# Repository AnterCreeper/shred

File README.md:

# SHRED: (S)ystem for (H)igh-performance (R)eal-time (E)lectric guitar (D)igital effects

If you have any questions, feel free to open Issues & PRs.

**WARNING! This project has not been fully tested in long-term production environments and is provided without warranty of any kind. Use at your own risk!**

## License

This project is licensed under the LGPL-2.1-or-later license.

**DO NOT** download or clone this project until you have read and agreed to the LICENSE.

## TODO

1. plug subboard designs
2. FPGA RTL integration
3. controller firmware

## Overview

This project implements an audio system for electric guitars and consists of essential components, including the hardware (core and plug) with Gerber files and schematics, digital logic designs, mechanical designs for the pickguard, and firmware for a low-power microcontroller that provides HMI and system controls.

The TFT screen is not included, which is from Waveshare ([Click here](https://www.waveshare.net/wiki/1.9inch_LCD_Module)) and would be easy to obtain.

## Functions

- Audio Record & Playback (SD Card)
- Audio Mixer
- USB Audio Input and Output
- Wireless BLE Real-time Audio Monitor
- Audio Effects (chorus, distortion, EQ...)

## Directory

### Core

This directory contains PCB designs (KiCad) for the main board, which implements most functions. It includes battery management (TI `BQ25601` charger with `TPD2S300` for Type-C PD high-voltage fast charging, and TI `BQ27720` energy gauge), system microcontroller (WCH `CH32X035`), FPGA unit (Gowin `Tang Primer 25K`), and the audio subsystem (ADI/Maxim `MAX9850` I2S DAC + onsemi `FAN3852` AFE+ADC to PDM, and Skyworks/Silicon Labs `Si5351` for clock generation). In addition, this system includes a BLE module (Nordic `nRF5340`) to provide ultra-low latency LE Audio streaming capability.

The power rails are carefully designed to provide long battery life. The system employs several load switches (MPS `MP5095` and Diodes `AP2151`) and ultra-low quiescent current regulators (TI `TPS62743` and `TPS7A20`), allowing specific components (keys and screen, audio system, flash storage, Bluetooth) to be shut down or set to low-power states.

The dual magnetic pickups are connected via IPEX-4 (some soldering work is required to modify the connection wires), which provides low-noise, pure raw signals.

### Plug

This directory contains PCB designs (KiCad) for the plug subboard, which includes an `audio jack`, `microSD slot`, `USB-C receptacle`, `charge indicator`, and `ambient light sensor`.

### RTL

This directory contains the audio processing logic:
- Core processor
- Audio synthesizer
- FLAC encoder & decoder
- Audio I/O interface
- USB device interface
- I2C device interface
- SD host controller interface

### Controller

This directory contains the system controller firmware, which sets up every device, monitors system states, renders the HMI, and reacts to user input events.

### LE-Audio

This directory contains the BLE module firmware subproject from a separate repository. It scans, connects, and pairs with earbuds, and then performs real-time audio streaming (LC3). This module acts as a peripheral to the system controller, communicating via a standard AT interface over UART.

### Others

Miscellaneous files under the root:
- `pickguard.dxf`: Pickguard CAD designs.
- `logo.jped`: Logo of `SHRED`, generated by Google NanoBanana 2.
- `logo.prompt`: Prompt of AI gen.

## Usage

**This section is W.I.P. and will be completed in the future.**

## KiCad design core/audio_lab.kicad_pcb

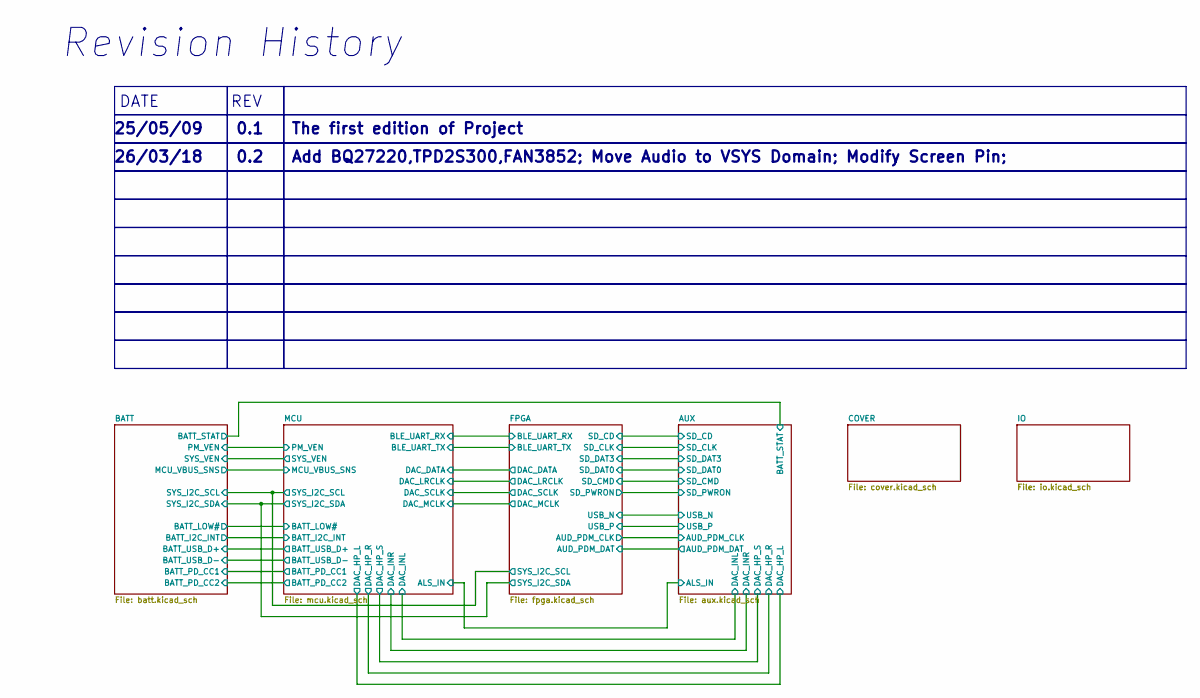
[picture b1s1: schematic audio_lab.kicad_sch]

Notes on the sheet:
Revision History
REV
0.2
Add BQ27220,TPD2S300,FAN3852; Move Audio to VSYS Domain; Modify Screen Pin;
0.1
25/05/09
The first edition of Project
DATE
26/03/18

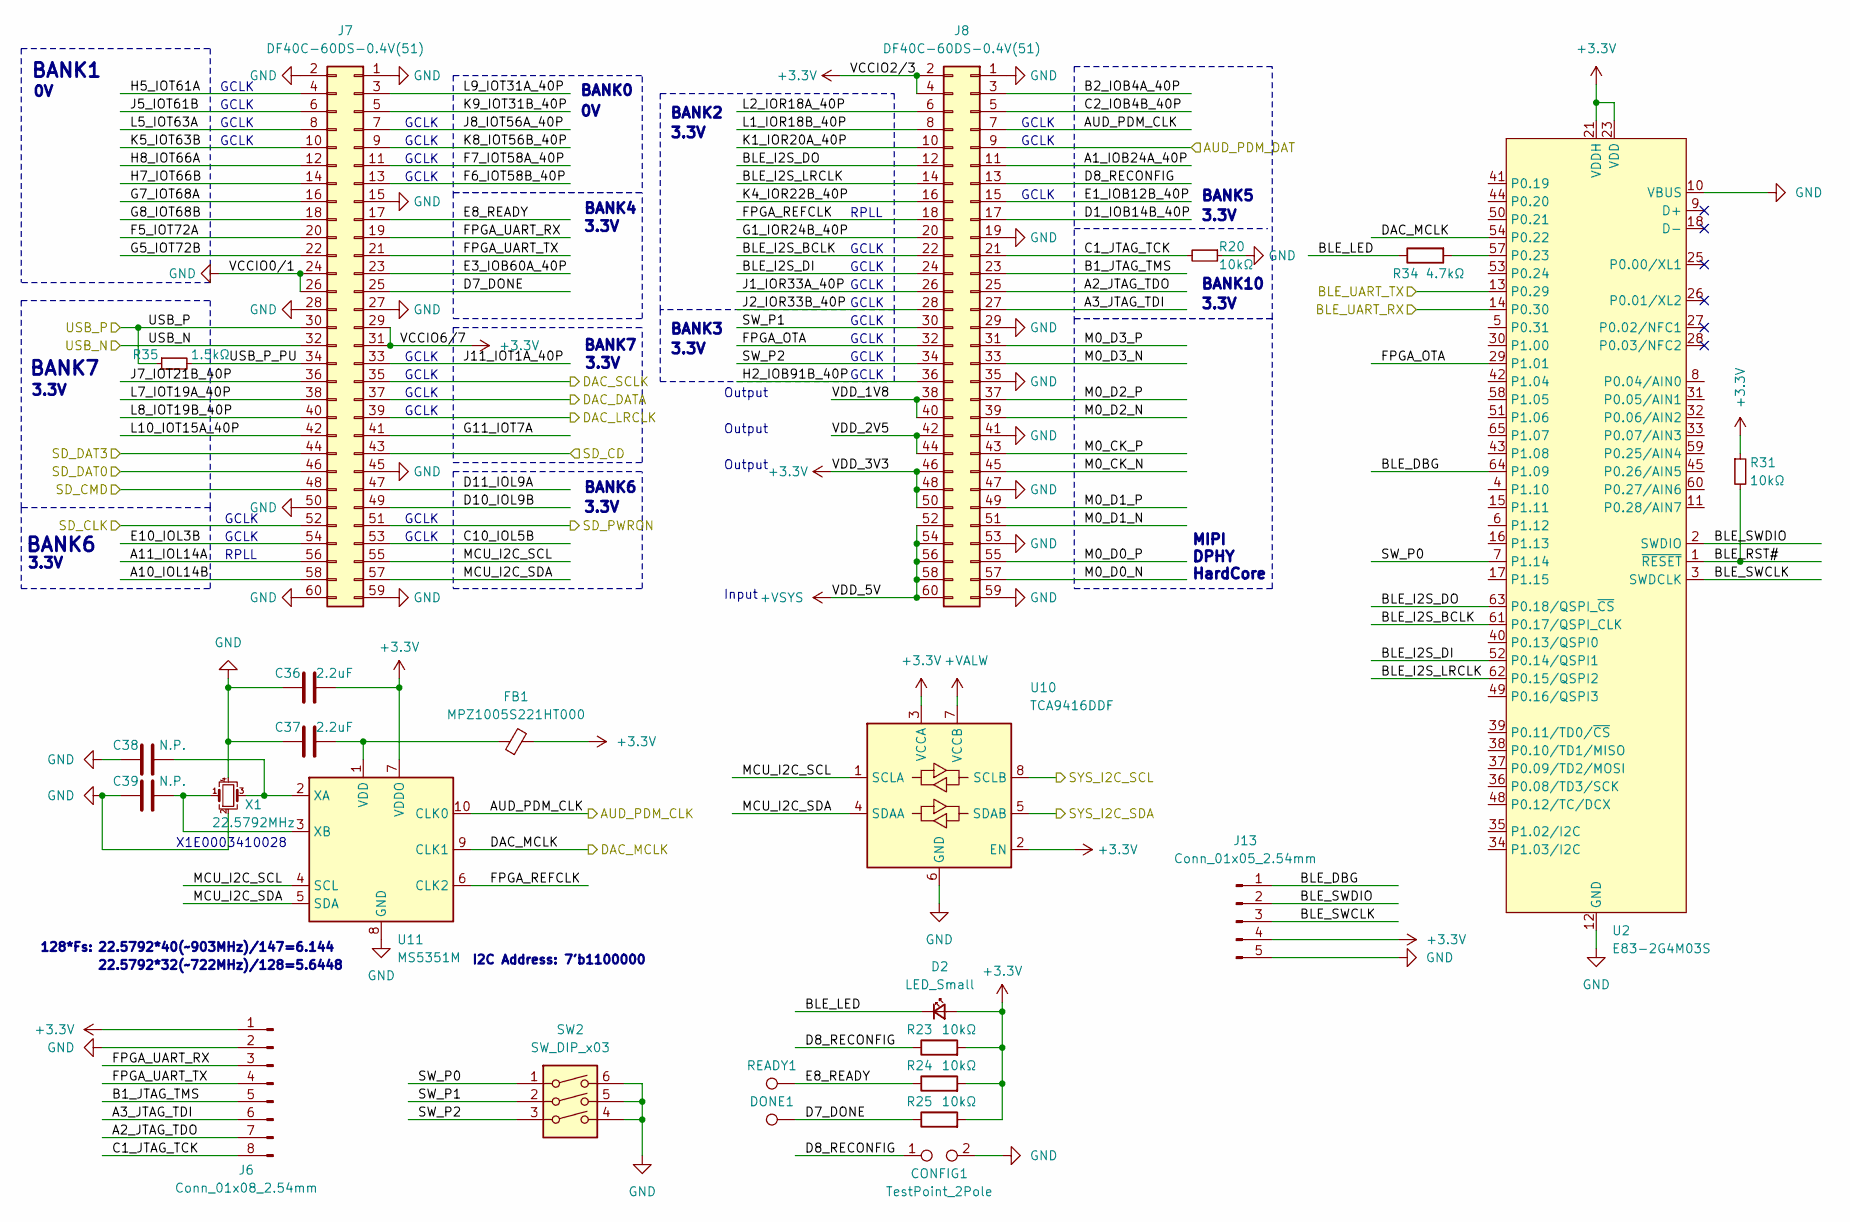
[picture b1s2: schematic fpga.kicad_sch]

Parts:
C36, C37: 2.2uF; C_0402_1005Metric
C38, C39: N.P.; C_0402_1005Metric
CONFIG1: TestPoint_2Pole; TestPoint_Bridge_Pitch2.0mm_Drill0.7mm
D2: LED_Small; D_0603_1608Metric
DONE1: TestPoint; TestPoint_Pad_D1.0mm
FB1: MPZ1005S221HT000; L_0402_1005Metric
J6: Conn_01x08_2.54mm; PinHeader_1x08_P2.54mm_Vertical
J7, J8: DF40C-60DS-0.4V(51); BTB-DF40C-60DS-0.4V(51)
J13: Conn_01x05_2.54mm; PinHeader_1x05_P2.54mm_Vertical
R20, R23, R24, R25, R31: 10kΩ; R_0402_1005Metric
R34: 4.7kΩ; R_0402_1005Metric
R35: 1.5kΩ; R_0402_1005Metric
READY1: TestPoint; TestPoint_Pad_D1.0mm
SW2: SW_DIP_x03; SW_DIP_SPSTx03_Slide_KingTek_DSHP03TS_W7.62mm_P1.27mm
U2: E83-2G4M03S; E83-2G4M03S_16x16mm_LGA; LCSC C5333991
U10: TCA9416DDF; TSOT-23-8
U11: MS5351M; MSOP-10_3x3mm_P0.5mm
X1: 22.5792MHz; Crystal_SMD_3225-4Pin_3.2x2.5mm

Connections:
+3.3V: C36.2, D2.2 (A), FB1.2, J6.1, J7.29, J7.31, J8.2, J8.4, J8.46, J8.48, J8.50, J13.4, R23.2, R24.2, R25.2, R31.1, U2.21 (VDDH), U2.23 (VDD), U10.2 (EN), U10.3 (VCCA), U11.7 (VDDO); also elsewhere on the board
+VALW: U10.7 (VCCB); also elsewhere on the board
+VSYS: J8.52, J8.54, J8.56, J8.58, J8.60; also elsewhere on the board
/AUX/AUD_PDM_DAT: J8.9; also elsewhere on the board
/AUX/SD_CD: J7.43; also elsewhere on the board
/AUX/SD_CLK: J7.52; also elsewhere on the board
/AUX/SD_CMD: J7.48; also elsewhere on the board
/AUX/SD_DAT0: J7.46; also elsewhere on the board
/AUX/SD_DAT3: J7.44; also elsewhere on the board
/AUX/SD_PWRON: J7.51; also elsewhere on the board
/BATT/SYS_I2C_SCL: U10.8 (SCLB); also elsewhere on the board
/BATT/SYS_I2C_SDA: U10.5 (SDAB); also elsewhere on the board
/FPGA/A1_IOB24A_40P: J8.11
/FPGA/A2_JTAG_TDO: J6.7, J8.25
/FPGA/A3_JTAG_TDI: J6.6, J8.27
/FPGA/A10_IOL14B: J7.58
/FPGA/A11_IOL14A: J7.56
/FPGA/AUD_PDM_CLK: J8.7, U11.10 (CLK0); also elsewhere on the board
/FPGA/B1_JTAG_TMS: J6.5, J8.23
/FPGA/B2_IOB4A_40P: J8.3
/FPGA/BLE_DBG: J13.1, U2.64 (P1.09)
/FPGA/BLE_I2S_BCLK: J8.22, U2.61 (P0.17/QSPI_CLK)
/FPGA/BLE_I2S_DI: J8.24, U2.52 (P0.14/QSPI1)
/FPGA/BLE_I2S_DO: J8.12, U2.63 (P0.18/QSPI_~CS)
/FPGA/BLE_I2S_LRCLK: J8.14, U2.62 (P0.15/QSPI2)
/FPGA/BLE_LED: D2.1 (K), R34.1
/FPGA/BLE_RST#: R31.2, U2.1 (~RESET)
/FPGA/BLE_SWCLK: J13.3, U2.3 (SWDCLK)
/FPGA/BLE_SWDIO: J13.2, U2.2 (SWDIO)
/FPGA/BLE_UART_RX: U2.14 (P0.30); also elsewhere on the board
/FPGA/BLE_UART_TX: U2.13 (P0.29); also elsewhere on the board
/FPGA/C1_JTAG_TCK: J6.8, J8.21, R20.2
/FPGA/C2_IOB4B_40P: J8.5
/FPGA/C10_IOL5B: J7.53
/FPGA/D1_IOB14B_40P: J8.17
/FPGA/D7_DONE: DONE1.1, J7.25, R25.1; also elsewhere on the board
/FPGA/D8_RECONFIG: CONFIG1.1, J8.13, R23.1; also elsewhere on the board
/FPGA/D10_IOL9B: J7.49
/FPGA/D11_IOL9A: J7.47
/FPGA/DAC_DATA: J7.37; also elsewhere on the board
/FPGA/DAC_LRCLK: J7.39; also elsewhere on the board
/FPGA/DAC_MCLK: U2.54 (P0.22), U11.9 (CLK1); also elsewhere on the board
/FPGA/DAC_SCLK: J7.35; also elsewhere on the board
/FPGA/E1_IOB12B_40P: J8.15
/FPGA/E3_IOB60A_40P: J7.23
/FPGA/E8_READY: J7.17, R24.1, READY1.1; also elsewhere on the board
/FPGA/E10_IOL3B: J7.54
/FPGA/F5_IOT72A: J7.20
/FPGA/F6_IOT58B_40P: J7.13
/FPGA/F7_IOT58A_40P: J7.11
/FPGA/FPGA_OTA: J8.32, U2.29 (P1.01)
/FPGA/FPGA_REFCLK: J8.18, U11.6 (CLK2)
/FPGA/FPGA_UART_RX: J6.3, J7.19
/FPGA/FPGA_UART_TX: J6.4, J7.21
/FPGA/G1_IOR24B_40P: J8.20
/FPGA/G5_IOT72B: J7.22
/FPGA/G7_IOT68A: J7.16
/FPGA/G8_IOT68B: J7.18
/FPGA/G11_IOT7A: J7.41
/FPGA/H2_IOB91B_40P: J8.36
/FPGA/H5_IOT61A: J7.4
/FPGA/H7_IOT66B: J7.14
/FPGA/H8_IOT66A: J7.12
/FPGA/J1_IOR33A_40P: J8.26
/FPGA/J2_IOR33B_40P: J8.28
/FPGA/J5_IOT61B: J7.6
/FPGA/J7_IOT21B_40P: J7.36
/FPGA/J8_IOT56A_40P: J7.7
/FPGA/J11_IOT1A_40P: J7.33
/FPGA/K1_IOR20A_40P: J8.10
/FPGA/K4_IOR22B_40P: J8.16
/FPGA/K5_IOT63B: J7.10
/FPGA/K8_IOT56B_40P: J7.9
/FPGA/K9_IOT31B_40P: J7.5
/FPGA/L1_IOR18B_40P: J8.8
/FPGA/L2_IOR18A_40P: J8.6
/FPGA/L5_IOT63A: J7.8
/FPGA/L7_IOT19A_40P: J7.38
/FPGA/L8_IOT19B_40P: J7.40
/FPGA/L9_IOT31A_40P: J7.3
/FPGA/L10_IOT15A_40P: J7.42
/FPGA/M0_CK_N: J8.45
/FPGA/M0_CK_P: J8.43
/FPGA/M0_D0_N: J8.57
/FPGA/M0_D0_P: J8.55
/FPGA/M0_D1_N: J8.51
/FPGA/M0_D1_P: J8.49
/FPGA/M0_D2_N: J8.39
/FPGA/M0_D2_P: J8.37
/FPGA/M0_D3_N: J8.33
/FPGA/M0_D3_P: J8.31
/FPGA/MCU_I2C_SCL: J7.55, U10.1 (SCLA), U11.4 (SCL)
/FPGA/MCU_I2C_SDA: J7.57, U10.4 (SDAA), U11.5 (SDA)
/FPGA/SW_P0: SW2.1, U2.7 (P1.14)
/FPGA/SW_P1: J8.30, SW2.2
/FPGA/SW_P2: J8.34, SW2.3
/FPGA/USB_N: J7.32; also elsewhere on the board
/FPGA/USB_P: J7.30, R35.1; also elsewhere on the board
/FPGA/USB_P_PU: J7.34, R35.2
/FPGA/VDD_1V8: J8.38, J8.40
/FPGA/VDD_2V5: J8.42, J8.44
GND: C36.1, C37.1, C38.1, C39.1, CONFIG1.2, J6.2, J7.1, J7.2, J7.15, J7.24, J7.26, J7.27, J7.28, J7.45, J7.50, J7.59, J7.60, J8.1, J8.19, J8.29, J8.35, J8.41, J8.47, J8.53, J8.59, J13.5, R20.1, SW2.4, SW2.5, SW2.6, U2.10 (VBUS), U2.12 (GND), U2.19 (GND), U2.20 (GND), U2.22 (GND), U2.24 (GND), U2.46 (GND), U2.47 (GND), U2.55 (GND), U2.56 (GND), U10.6 (GND), U11.8 (GND), X1.2, X1.4; also elsewhere on the board
unnamed: R34.2, U2.57 (P0.23)
unnamed: C37.2, FB1.1, U11.1 (VDD)
unnamed: C38.2, U11.2 (XA), X1.3
unnamed: C39.2, U11.3 (XB), X1.1

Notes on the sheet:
GCLK
BANK6
RPLL
BANK2
22.5792*32(~722MHz)/128=5.6448
3.3V
BANK10
MIPI DPHY HardCore
BANK4
BANK5
X1E0003410028
Input
Output
BANK7
I2C Address: 7'b1100000
128*Fs:
BANK1
22.5792*40(~903MHz)/147=6.144
BANK3
BANK0

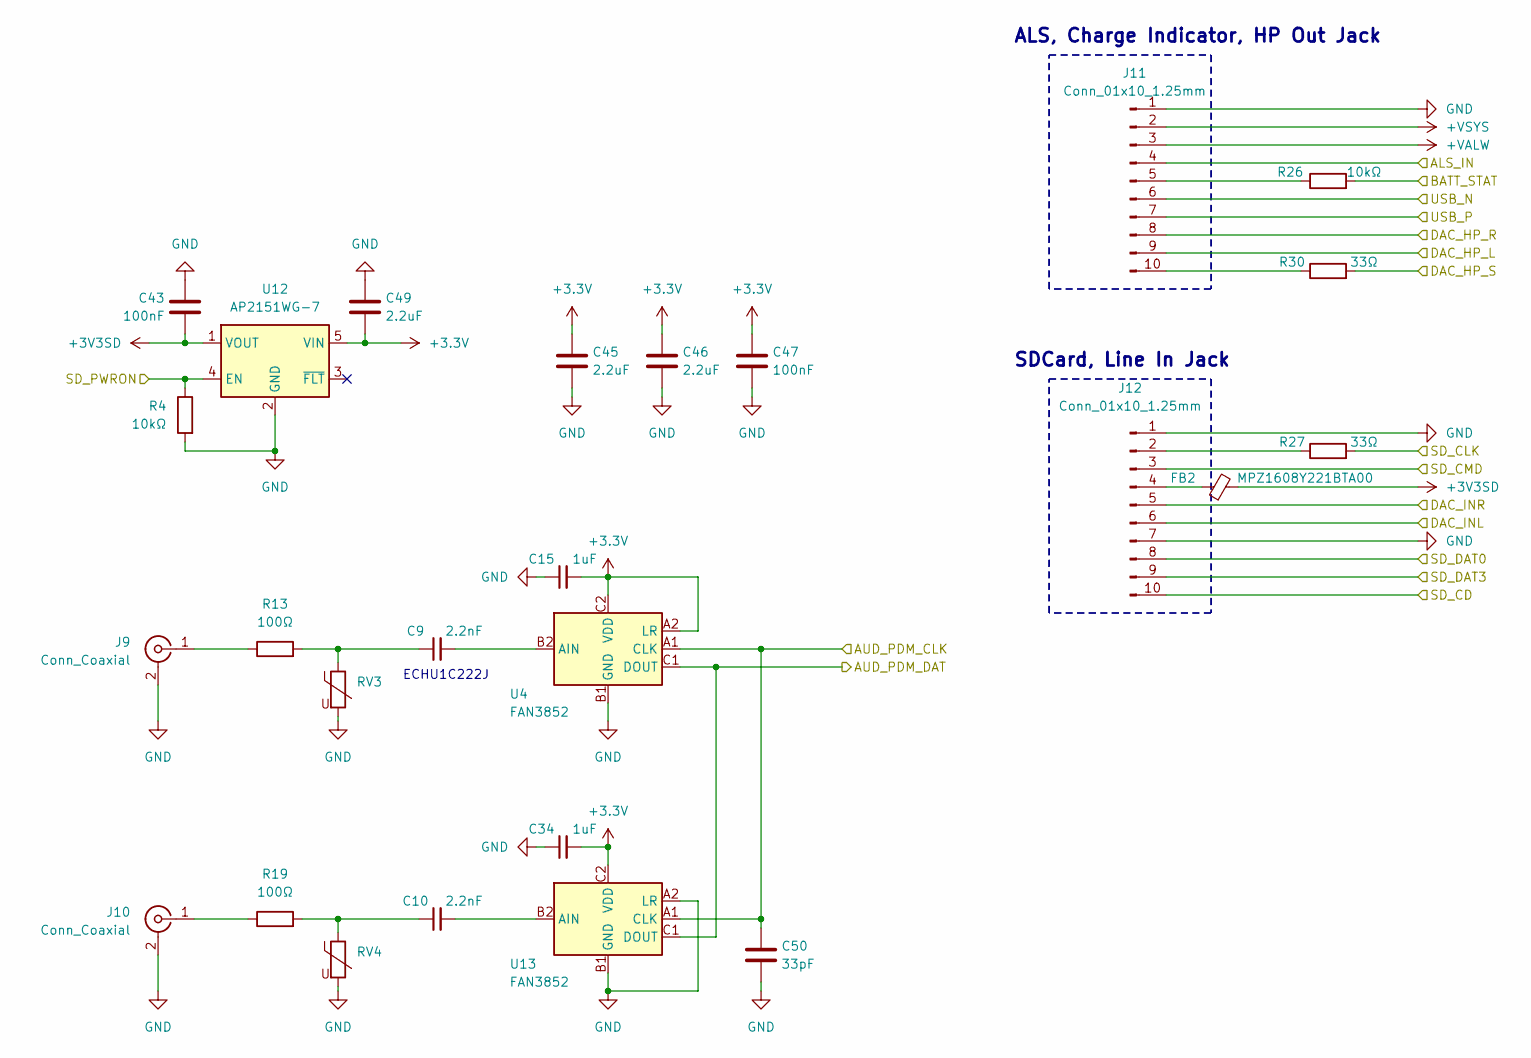
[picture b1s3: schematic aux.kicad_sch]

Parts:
C9, C10: 2.2nF; C_0603_1608Metric
C15, C34: 1uF; C_0402_1005Metric
C43, C47: 100nF; C_0402_1005Metric
C45, C46, C49: 2.2uF; C_0402_1005Metric
C50: 33pF; C_0402_1005Metric
FB2: MPZ1608Y221BTA00; L_0603_1608Metric
J9, J10: Conn_Coaxial; IPEX_20449-001E-03
J11, J12: Conn_01x10_1.25mm; Molex_PicoBlade_53047-1010_1x10_P1.25mm_Vertical
R4, R26: 10kΩ; R_0402_1005Metric
R13, R19: 100Ω; R_0402_1005Metric
R27, R30: 33Ω; R_0402_1005Metric
RV3, RV4: Varistor; R_0402_1005Metric
U4, U13: FAN3852; Texas_DSBGA-6_0.855x1.255mm_Layout2x3_P0.4mm_LevelC
U12: AP2151WG-7; SOT-23-5

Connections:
+3.3V: C15.2, C34.2, C45.1, C46.1, C47.1, C49.2, U4.A2 (LR), U4.C2 (VDD), U12.5 (VIN), U13.C2 (VDD); also elsewhere on the board
+3V3SD: C43.2, FB2.2, U12.1 (VOUT)
+VALW: J11.3; also elsewhere on the board
+VSYS: J11.2; also elsewhere on the board
/AUX/ALS_IN: J11.4; also elsewhere on the board
/AUX/AUD_PDM_DAT: U4.C1 (DOUT), U13.C1 (DOUT); also elsewhere on the board
/AUX/BATT_STAT: R26.2; also elsewhere on the board
/AUX/DAC_HP_L: J11.9; also elsewhere on the board
/AUX/DAC_HP_R: J11.8; also elsewhere on the board
/AUX/DAC_HP_S: R30.2; also elsewhere on the board
/AUX/DAC_INL: J12.6; also elsewhere on the board
/AUX/DAC_INR: J12.5; also elsewhere on the board
/AUX/SD_CD: J12.10; also elsewhere on the board
/AUX/SD_CLK: R27.2; also elsewhere on the board
/AUX/SD_CMD: J12.3; also elsewhere on the board
/AUX/SD_DAT0: J12.8; also elsewhere on the board
/AUX/SD_DAT3: J12.9; also elsewhere on the board
/AUX/SD_PWRON: R4.1, U12.4 (EN); also elsewhere on the board
/FPGA/AUD_PDM_CLK: C50.1, U4.A1 (CLK), U13.A1 (CLK); also elsewhere on the board
/FPGA/USB_N: J11.6; also elsewhere on the board
/FPGA/USB_P: J11.7; also elsewhere on the board
GND: C15.1, C34.1, C43.1, C45.2, C46.2, C47.2, C49.1, C50.2, J9.2 (Ext), J10.2 (Ext), J11.1, J12.1, J12.7, R4.2, RV3.2, RV4.2, U4.B1 (GND), U12.2 (GND), U13.A2 (LR), U13.B1 (GND); also elsewhere on the board
unnamed: C9.1, R13.2, RV3.1
unnamed: C10.1, R19.2, RV4.1
unnamed: J9.1 (In), R13.1
unnamed: J10.1 (In), R19.1
unnamed: J11.5, R26.1
unnamed: J11.10, R30.1
unnamed: J12.2, R27.1
unnamed: FB2.1, J12.4
unnamed: C9.2, U4.B2 (AIN)
unnamed: C10.2, U13.B2 (AIN)

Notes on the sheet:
ECHU1C222J
SDCard, Line In Jack
ALS, Charge Indicator, HP Out Jack

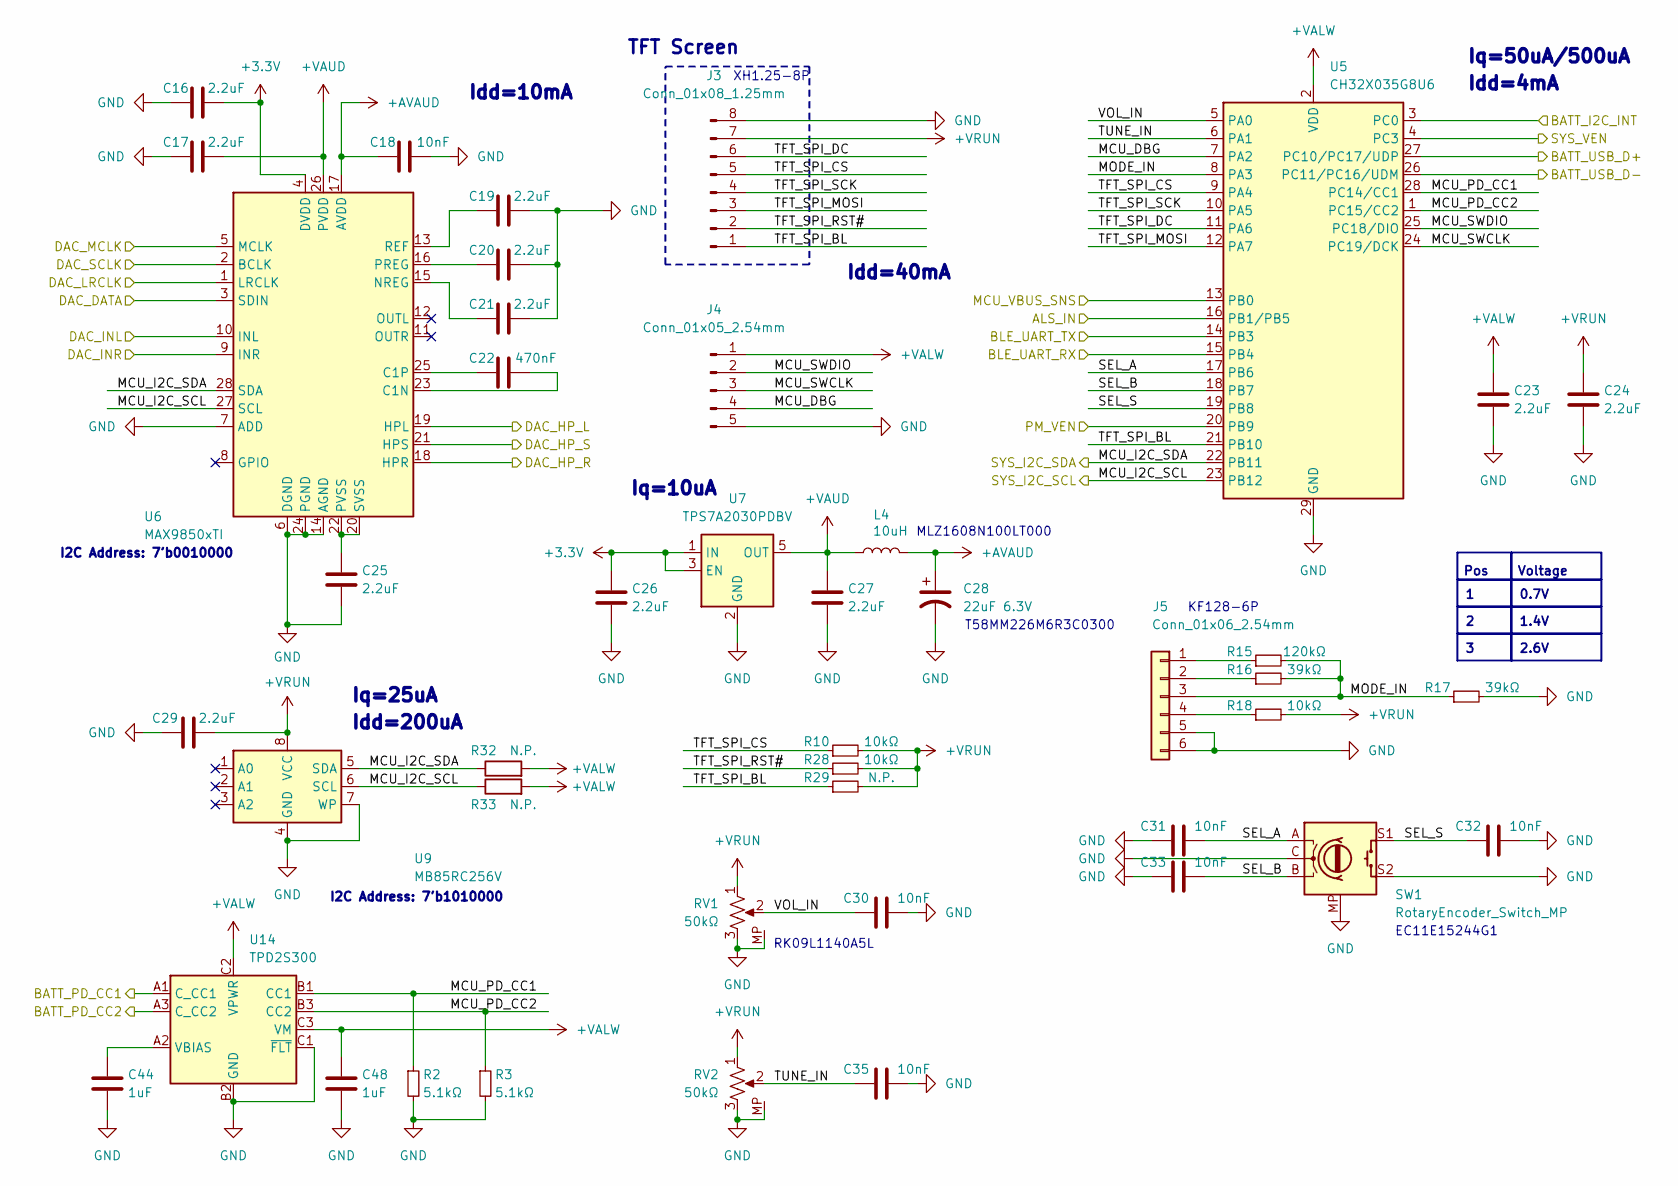
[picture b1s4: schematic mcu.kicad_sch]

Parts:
C16, C17, C19, C20, C21, C23, C24, C25, C26, C27, C29: 2.2uF; C_0402_1005Metric
C18, C30, C31, C32, C33, C35: 10nF; C_0402_1005Metric
C22: 470nF; C_0402_1005Metric
C28: 22uF 6.3V; CP_EIA-1608-08_AVX-J
C44, C48: 1uF; C_0402_1005Metric
J3: Conn_01x08_1.25mm; Molex_PicoBlade_53047-0810_1x08_P1.25mm_Vertical
J4: Conn_01x05_2.54mm; PinHeader_1x05_P2.54mm_Vertical
J5: Conn_01x06_2.54mm; PinSocket_1x06_P2.54mm_Vertical
L4: 10uH; L_0603_1608Metric
R2, R3: 5.1kΩ; R_0402_1005Metric
R10, R18, R28: 10kΩ; R_0402_1005Metric
R15: 120kΩ; R_0402_1005Metric
R16, R17: 39kΩ; R_0402_1005Metric
R29, R32, R33: N.P.; R_0402_1005Metric
RV1, RV2: 50kΩ; Potentiometer_Alpha_RD901F-40-00D_Single_Vertical
SW1: RotaryEncoder_Switch_MP; RotaryEncoder_Favor_FEC11_Vertical_H15mm
U5: CH32X035G8U6; QFN-28-1EP_4x4mm_P0.4mm_EP2.7x2.7mm
U6: MAX9850xTI; TQFN-28-1EP_5x5mm_P0.5mm_EP3.25x3.25mm_ThermalVias
U7: TPS7A2030PDBV; SOT-23-5
U9: MB85RC256V; SOIC-8_3.9x4.9mm_P1.27mm
U14: TPD2S300; Texas_DSBGA-9_1.36x1.36mm_Layout3x3_P0.4mm

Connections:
+3.3V: C16.2, C26.1, U6.4 (DVDD), U7.1 (IN), U7.3 (EN); also elsewhere on the board
+AVAUD: C18.1, C28.1, L4.2, U6.17 (AVDD)
+VALW: C23.1, C48.1, J4.1, R32.2, R33.2, U5.2 (VDD), U14.C2 (VPWR), U14.C3 (VM); also elsewhere on the board
+VAUD: C17.2, C27.1, L4.1, U6.26 (PVDD), U7.5 (OUT)
+VRUN: C24.1, C29.2, J3.7, R10.2, R18.2, R28.2, R29.2, RV1.1, RV2.1, U9.8 (VCC); also elsewhere on the board
/AUX/ALS_IN: U5.16 (PB1/PB5); also elsewhere on the board
/AUX/DAC_HP_L: U6.19 (HPL); also elsewhere on the board
/AUX/DAC_HP_R: U6.18 (HPR); also elsewhere on the board
/AUX/DAC_HP_S: U6.21 (HPS); also elsewhere on the board
/AUX/DAC_INL: U6.10 (INL); also elsewhere on the board
/AUX/DAC_INR: U6.9 (INR); also elsewhere on the board
/BATT/BATT_I2C_INT: U5.3 (PC0); also elsewhere on the board
/BATT/BATT_PD_CC1: U14.A1 (C_CC1); also elsewhere on the board
/BATT/BATT_PD_CC2: U14.A3 (C_CC2); also elsewhere on the board
/BATT/BATT_USB_D+: U5.27 (PC10/PC17/UDP); also elsewhere on the board
/BATT/BATT_USB_D-: U5.26 (PC11/PC16/UDM); also elsewhere on the board
/BATT/MCU_VBUS_SNS: U5.13 (PB0); also elsewhere on the board
/BATT/PM_VEN: U5.20 (PB9); also elsewhere on the board
/BATT/SYS_I2C_SCL: R33.1, U5.23 (PB12), U6.27 (SCL), U9.6 (SCL); also elsewhere on the board
/BATT/SYS_I2C_SDA: R32.1, U5.22 (PB11), U6.28 (SDA), U9.5 (SDA); also elsewhere on the board
/BATT/SYS_VEN: U5.4 (PC3); also elsewhere on the board
/FPGA/BLE_UART_RX: U5.15 (PB4); also elsewhere on the board
/FPGA/BLE_UART_TX: U5.14 (PB3); also elsewhere on the board
/FPGA/DAC_DATA: U6.3 (SDIN); also elsewhere on the board
/FPGA/DAC_LRCLK: U6.1 (LRCLK); also elsewhere on the board
/FPGA/DAC_MCLK: U6.5 (MCLK); also elsewhere on the board
/FPGA/DAC_SCLK: U6.2 (BCLK); also elsewhere on the board
/MCU/MCU_DBG: J4.4, U5.7 (PA2)
/MCU/MCU_PD_CC1: R2.1, U5.28 (PC14/CC1), U14.B1 (CC1)
/MCU/MCU_PD_CC2: R3.1, U5.1 (PC15/CC2), U14.B3 (CC2)
/MCU/MCU_SWCLK: J4.3, U5.24 (PC19/DCK)
/MCU/MCU_SWDIO: J4.2, U5.25 (PC18/DIO)
/MCU/MODE_IN: J5.3, R15.2, R16.2, R17.1, U5.8 (PA3)
/MCU/SEL_A: C31.2, SW1.A, U5.17 (PB6)
/MCU/SEL_B: C33.2, SW1.B, U5.18 (PB7)
/MCU/SEL_S: C32.1, SW1.S1, U5.19 (PB8)
/MCU/TFT_SPI_BL: J3.1, R29.1, U5.21 (PB10)
/MCU/TFT_SPI_CS: J3.5, R10.1, U5.9 (PA4)
/MCU/TFT_SPI_DC: J3.6, U5.11 (PA6)
/MCU/TFT_SPI_MOSI: J3.3, U5.12 (PA7)
/MCU/TFT_SPI_RST#: J3.2, R28.1
/MCU/TFT_SPI_SCK: J3.4, U5.10 (PA5)
/MCU/TUNE_IN: C35.1, RV2.2, U5.6 (PA1)
/MCU/VOL_IN: C30.1, RV1.2, U5.5 (PA0)
GND: C16.1, C17.1, C18.2, C19.2, C20.2, C21.2, C23.2, C24.2, C25.2, C26.2, C27.2, C28.2, C29.1, C30.2, C31.1, C32.2, C33.1, C35.2, C44.2, C48.2, J3.8, J4.5, J5.5, J5.6, R2.2, R3.2, R17.2, RV1.3, RV1.MP, RV2.3, RV2.MP, SW1.C, SW1.MP, SW1.S2, U5.29 (GND), U6.6 (DGND), U6.7 (ADD), U6.14 (AGND), U6.24 (PGND), U6.29 (AGND), U7.2 (GND), U9.4 (GND), U9.7 (WP), U14.B2 (GND), U14.C1 (~FLT); also elsewhere on the board
unnamed: J5.1, R15.1
unnamed: J5.2, R16.1
unnamed: J5.4, R18.1
unnamed: C22.2, U6.23 (C1N)
unnamed: C22.1, U6.25 (C1P)
unnamed: C21.1, U6.15 (NREG)
unnamed: C20.1, U6.16 (PREG)
unnamed: C25.1, U6.20 (SVSS), U6.22 (PVSS)
unnamed: C19.1, U6.13 (REF)
unnamed: C44.1, U14.A2 (VBIAS)

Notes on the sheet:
T58MM226M6R3C0300
Idd=4mA
TFT Screen
Pos
Iq=50uA/500uA
XH1.25-8P
RK09L1140A5L
MLZ1608N100LT000
0.7V
1.4V
Idd=200uA
Idd=10mA
Iq=10uA
Iq=25uA
2.6V
I2C Address: 7'b1010000
Voltage
I2C Address: 7'b0010000
Idd=40mA
KF128-6P
EC11E15244G1

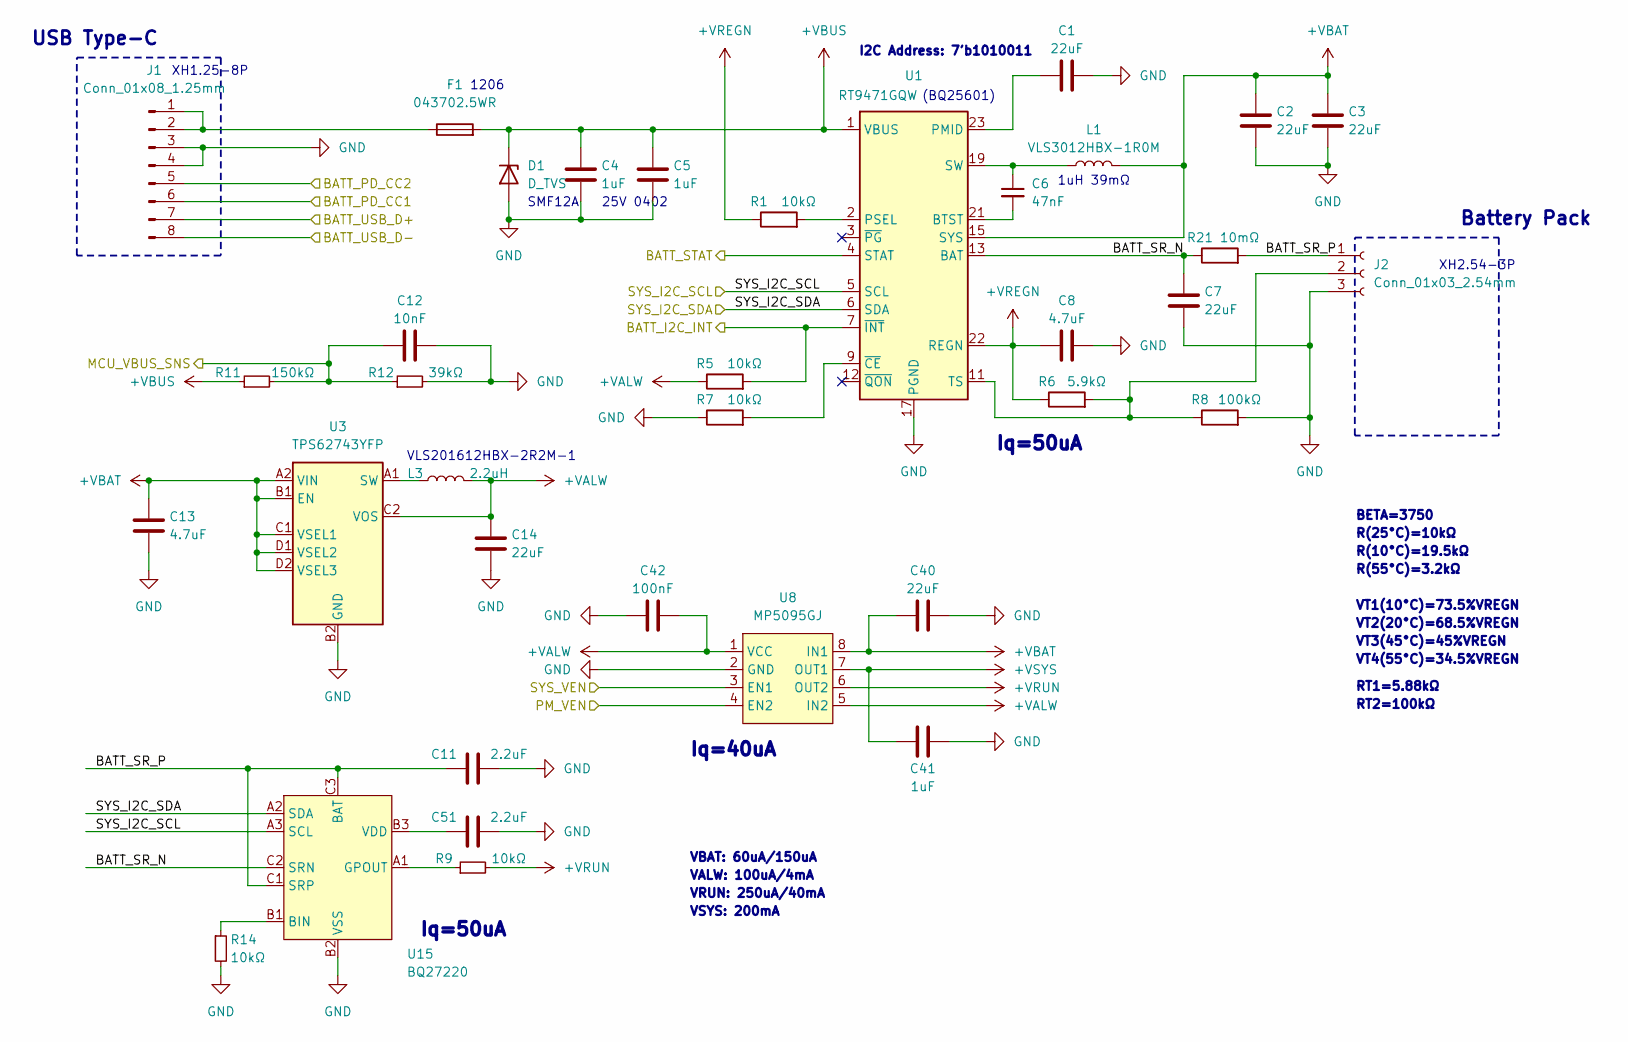
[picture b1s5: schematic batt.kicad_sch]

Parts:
C1, C2, C3, C7, C14, C40: 22uF; C_0603_1608Metric
C4, C5, C41: 1uF; C_0402_1005Metric
C6: 47nF; C_0402_1005Metric
C8, C13: 4.7uF; C_0402_1005Metric
C11, C51: 2.2uF; C_0402_1005Metric
C12: 10nF; C_0402_1005Metric
C42: 100nF; C_0402_1005Metric
D1: D_TVS; D_PowerDI-123
F1: 043702.5WR; Fuse_1206_3216Metric
J1: Conn_01x08_1.25mm; Molex_PicoBlade_53047-0810_1x08_P1.25mm_Vertical
J2: Conn_01x03_2.54mm; JST_XH_B3B-XH-A_1x03_P2.50mm_Vertical
L1: VLS3012HBX-1R0M; L_TDK_VLS3012HBX
L3: 2.2uH; L_Murata_DFE201610P
R1, R5, R7, R9, R14: 10kΩ; R_0402_1005Metric
R6: 5.9kΩ; R_0402_1005Metric
R8: 100kΩ; R_0402_1005Metric
R11: 150kΩ; R_0402_1005Metric
R12: 39kΩ; R_0402_1005Metric
R21: 10mΩ; R_1206_3216Metric
U1: RT9471GQW; RICKTEK_WQFN-24-1EP_4x4mm_P0.5mm_EP2.6x2.6mm_ThermalVias
U3: TPS62743YFP; Texas_DSBGA-8_0.86x1.56mm_Layout2x4_P0.4mm
U8: MP5095GJ; TSOT-23-8
U15: BQ27220; Texas_DSBGA-9_1.62x1.58mm_Layout3x3_P0.5mm

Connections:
+VALW: C14.1, C42.2, L3.2, R5.1, U3.C2 (VOS), U8.1 (VCC), U8.5 (IN2); also elsewhere on the board
+VBAT: C2.1, C3.1, C13.1, C40.1, L1.2, U1.15 (SYS), U1.16 (SYS), U3.A2 (VIN), U3.B1 (EN), U3.C1 (VSEL1), U3.D1 (VSEL2), U3.D2 (VSEL3), U8.8 (IN1)
+VBUS: C4.1, C5.1, D1.1 (K), F1.2, R11.1, U1.1 (VBUS), U1.24 (VBUS)
+VREGN: C8.1, R1.1, R6.1, U1.22 (REGN)
+VRUN: R9.2, U8.6 (OUT2); also elsewhere on the board
+VSYS: C41.1, U8.7 (OUT1); also elsewhere on the board
/AUX/BATT_STAT: U1.4 (STAT); also elsewhere on the board
/BATT/BATT_I2C_INT: R5.2, U1.7 (~INT); also elsewhere on the board
/BATT/BATT_PD_CC1: J1.6; also elsewhere on the board
/BATT/BATT_PD_CC2: J1.5; also elsewhere on the board
/BATT/BATT_SR_N: C7.1, R21.1, U1.13 (BAT), U1.14 (BAT), U15.C2 (SRN)
/BATT/BATT_SR_P: C11.1, J2.1, R21.2, U15.C1 (SRP), U15.C3 (BAT)
/BATT/BATT_USB_D+: J1.7; also elsewhere on the board
/BATT/BATT_USB_D-: J1.8; also elsewhere on the board
/BATT/MCU_VBUS_SNS: C12.1, R11.2, R12.1; also elsewhere on the board
/BATT/PM_VEN: U8.4 (EN2); also elsewhere on the board
/BATT/SYS_I2C_SCL: U1.5 (SCL), U15.A3 (SCL); also elsewhere on the board
/BATT/SYS_I2C_SDA: U1.6 (SDA), U15.A2 (SDA); also elsewhere on the board
/BATT/SYS_VEN: U8.3 (EN1); also elsewhere on the board
GND: C1.2, C2.2, C3.2, C4.2, C5.2, C7.2, C8.2, C11.2, C12.2, C13.2, C14.2, C40.2, C41.2, C42.1, C51.2, D1.2 (A), J1.3, J1.4, J2.3, R7.1, R8.2, R12.2, R14.2, U1.17 (PGND), U1.18 (PGND), U1.25 (PGND), U3.B2 (GND), U8.2 (GND), U15.B2 (VSS); also elsewhere on the board
unnamed: C6.1, L1.1, U1.19 (SW), U1.20 (SW)
unnamed: F1.1, J1.1, J1.2
unnamed: J2.2, R6.2, R8.1, U1.11 (TS)
unnamed: C6.2, U1.21 (BTST)
unnamed: C1.1, U1.23 (PMID)
unnamed: R1.2, U1.2 (PSEL)
unnamed: R7.2, U1.9 (~CE)
unnamed: L3.1, U3.A1 (SW)
unnamed: R14.1, U15.B1 (BIN)
unnamed: R9.1, U15.A1 (GPOUT)
unnamed: C51.1, U15.B3 (VDD)

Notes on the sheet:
1uH 39mΩ
RT2=100kΩ
VT2(20°C)=68.5%VREGN
Iq=40uA
XH2.54-3P
VSYS: 200mA
BETA=3750
VLS201612HBX-2R2M-1
VT4(55°C)=34.5%VREGN
Iq=50uA
25V 0402
VT1(10°C)=73.5%VREGN
USB Type-C
XH1.25-8P
RT1=5.88kΩ
(BQ25601)
VT3(45°C)=45%VREGN
VALW: 100uA/4mA
R(10°C)=19.5kΩ
1206
R(55°C)=3.2kΩ
VBAT: 60uA/150uA
R(25°C)=10kΩ
I2C Address: 7'b1010011
SMF12A
VRUN: 250uA/40mA
Battery Pack

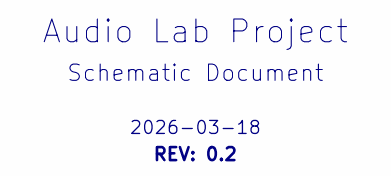
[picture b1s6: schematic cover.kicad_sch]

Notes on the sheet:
2026-03-18
Schematic Document
REV: 0.2
Audio Lab Project

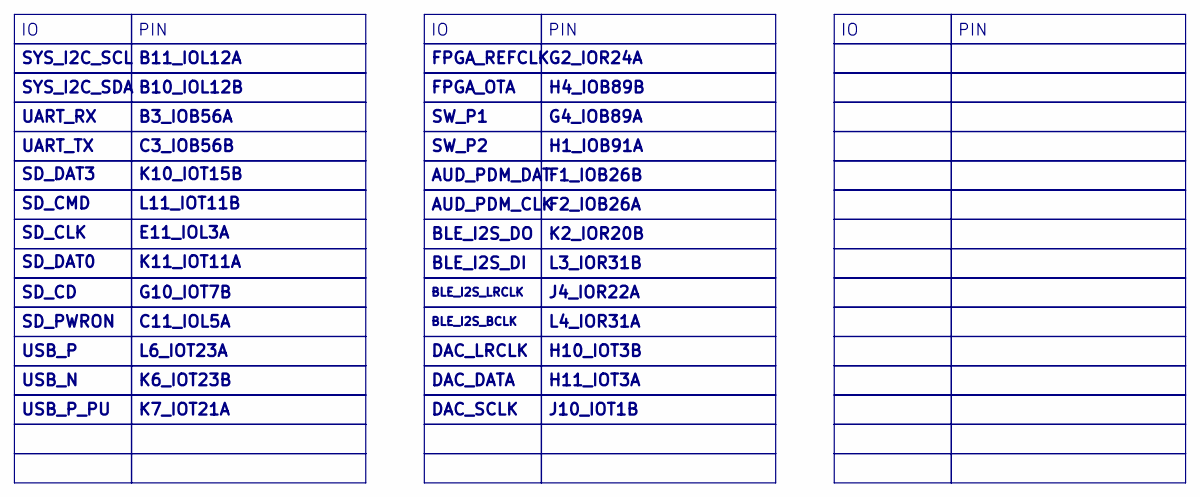
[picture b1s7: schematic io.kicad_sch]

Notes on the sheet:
L4_IOR31A
SD_PWRON
BLE_I2S_LRCLK
UART_RX
L6_IOT23A
SD_CD
AUD_PDM_DAT
SYS_I2C_SDA
K2_IOR20B
H10_IOT3B
J4_IOR22A
DAC_SCLK
G10_IOT7B
K6_IOT23B
SYS_I2C_SCL
E11_IOL3A
G2_IOR24A
G4_IOB89A
C3_IOB56B
K10_IOT15B
DAC_LRCLK
K7_IOT21A
USB_P
DAC_DATA
L3_IOR31B
BLE_I2S_DO
FPGA_OTA
PIN
L11_IOT11B
K11_IOT11A
F1_IOB26B
B3_IOB56A
BLE_I2S_BCLK
B10_IOL12B
UART_TX
H11_IOT3A
SD_CMD
SD_DAT0
USB_N
C11_IOL5A

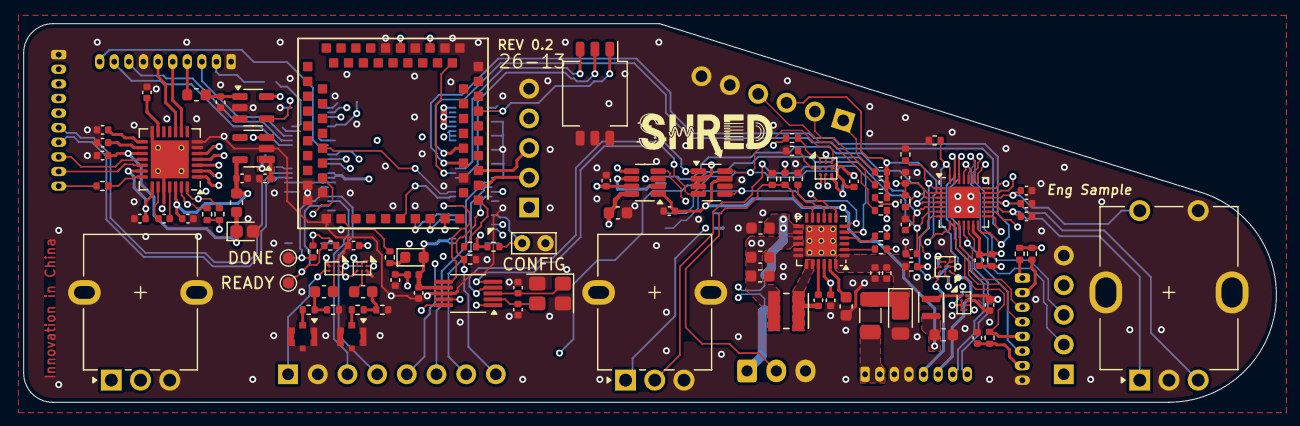
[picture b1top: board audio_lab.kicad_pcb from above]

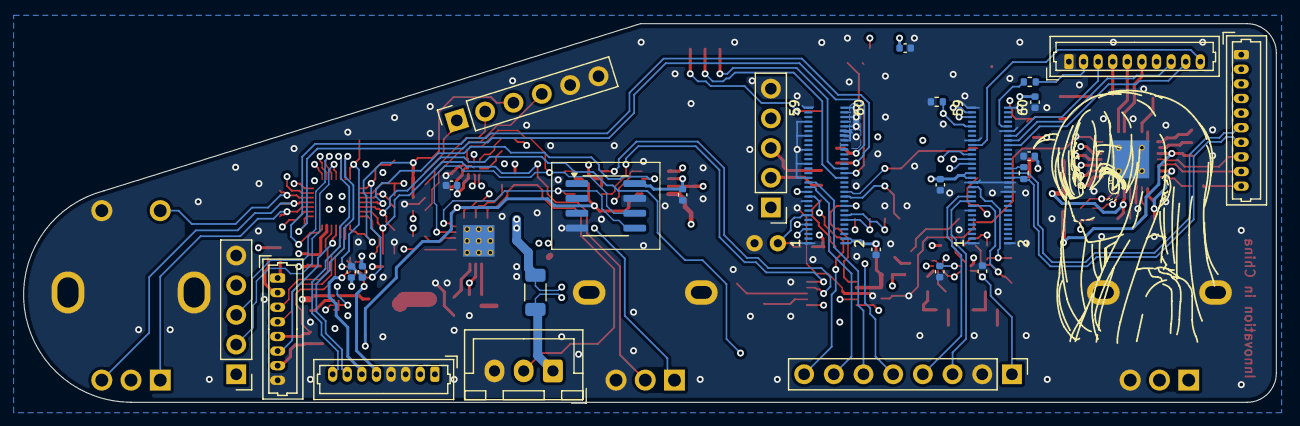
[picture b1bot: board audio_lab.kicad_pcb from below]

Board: 4 copper layers, 107.2 x 32.4 mm, 131 parts (27 on the bottom side), 126 nets.

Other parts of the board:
CONFIG: TestPoint_2Pole; TestPoint_Bridge_Pitch2.0mm_Drill0.7mm
DONE: TestPoint; TestPoint_Pad_D1.0mm
READY: TestPoint; TestPoint_Pad_D1.0mm

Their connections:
/FPGA/D7_DONE: DONE.1; also elsewhere on the board
/FPGA/D8_RECONFIG: CONFIG.1; also elsewhere on the board
/FPGA/E8_READY: READY.1; also elsewhere on the board
GND: CONFIG.2; also elsewhere on the board
